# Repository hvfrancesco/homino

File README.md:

Homino
======

What is Homino?
---------------

Homino is a diy Arduino Duemilanove/Uno compatible board with some moloko vellocet addition
(e.g. featuring on-board 433Mhz RF transceiver for experiments on home-automation and microcontroller communication).
Homino is an open-hardware project by HVA (http://www.hv-a.com)

The board is based on Arduino open-hardware design, but revised in order to be made using a single-sided copper board and low-tech techniques like toner-transfer etching.
The connectors in Homino are arduino shields compatible, but the board comes in Altoids tin can format, so you can have the mints while soldering all those little components.

How does Homino compare to Arduino?
-----------------------------------

Homino replicates almost all the features of Atmega328 based Arduino, with a few design limitations:

- No on-board usb-to-ttl, you will need an external usb-ttl cable to program it or a serial port adapter that can handle RS232 level switching (however auto-reset works flawlessly)
- No ISP connector

There is fortunately some nice additions too:

- Selectable 5V/3.3V operation mode (through an old style jumper, we feared a slide switch could be more dangerous)
- On-board RF communication based on low-cost 433Mhz radio modules like the ones from SeeedStudio, allowing the interoperability with current low-cost 433 MHz remote controlled devices. Homino will most likely work with all 433Mhz popular power outlet sockets.
Communication between several Homino boards or any other 433Mhz RF enabled microcontroller is also very easily done through VirtualWire library.

How do I build Homino?
----------------------

Homino is designed to be built on a homemade custom produced pcb using single sided boards.
We successfully built several boards using tone-transfer method using a photocopier and common light magazine coated paper, you can use transparency film, but the magazine solution proved to be the most reliable and cheapest in our experience.
Homino board is rather dense and has some thin routes and small gaps between them, so it is not the easiest design to use with tone-transfer based etching, but if you're careful it works very well.

List of components:

- PCB single sided board (you can cut 3 Homino boards from a 160x100 sheet)
- 1 x Atmega328 MCU (use Atmega328P-PU for lower power consumption, Atmega328-PU will work fine anyway)
- 1 x 28 way DIL socket (optional but useful if you plan to remove or change the Atmega chip)
- 3 x 47uF capacitors
- 5 x 0,1 uF ceramic capacitors
- 2 x 22 pF ceramic capacitors
- 1 x 5V voltage regulator (7805 in TO-220 case)
- 1 x 3.3 V voltage regulator (LP2950 in TO-92 case)
- 1 x N4001 diode
- 2 x 1k resistor
- 1 x 10k resistor
- 2 x leds (using a blue led for power and a red one linked to digital pin13)
- 1 x 16Mhz crystal (a cheaper 16
Mhz ceramic resonator can be used, you could choose a 3-pin resonator and in that case you can probably omit the 22pF capacitors, but we like the crystal better)
- 1 power jack (optional)
- female pin sockets
- 1 x 6 way male pin header
- 1 x 3 way male pin header with jumper
- 1 x button for reset
- RF transmitter and receiver modules

The cost of the components is about 9,5 euros when bought in very small quantities from online distributors like Farnell or RS, if you buy larger quantities or have cheaper providers, the total cost can be quite lower. RF modules from SeeedStudio cost $4,9.
Ideal cost including RF modules should be around 12 US$.
You can buy Atmega328 chip already programmed with Arduino bootloader from several distributors or Arduino online store, but if you already own an Arduino or some kind of AVR programmer you can buy bare 328 chip and save a few euros. Burning the bootloader to an Atmega using another Arduino as ISP programmer, even if you are new to Arduino world, is a piece of cake if you follow this tutorial:
http://arduino.cc/en/Tutorial/ArduinoToBreadboard

The following image is a label you can simply print on self-adhesive paper and stick on top of your Homino board before soldering the components.

Useful links
------------

Arduino libraries for RF projects
- http://code.google.com/p/rc-switch/
- http://www.airspayce.com/mikem/arduino/

Low-cost RF modules compatible with Homino
- http://www.seeedstudio.com/depot/433mhz-rf-link-kit-p-127.html?cPath=19_22

Credits
-------

Homino is obviously Open Hardware, and all the files are distributed under a
<a rel="license" href="http://creativecommons.org/licenses/by-nc-sa/3.0/">Creative Commons Attribution-NonCommercial-ShareAlike 3.0 Unported License</a>
.

HVA lego-logo is property of 'HVA - hermanitos verdes architetti' (http://www.hv-a.com) and shouldn't be used without permission.

Homino is inspired and based on other Arduino compatible projects, for example:

http://hacks.ayars.org/2013/05/ayrduino-single-sided-arduino-clone.html
http://vonkonow.com/wordpress/2012/10/nanino-the-diy-friendly-arduino

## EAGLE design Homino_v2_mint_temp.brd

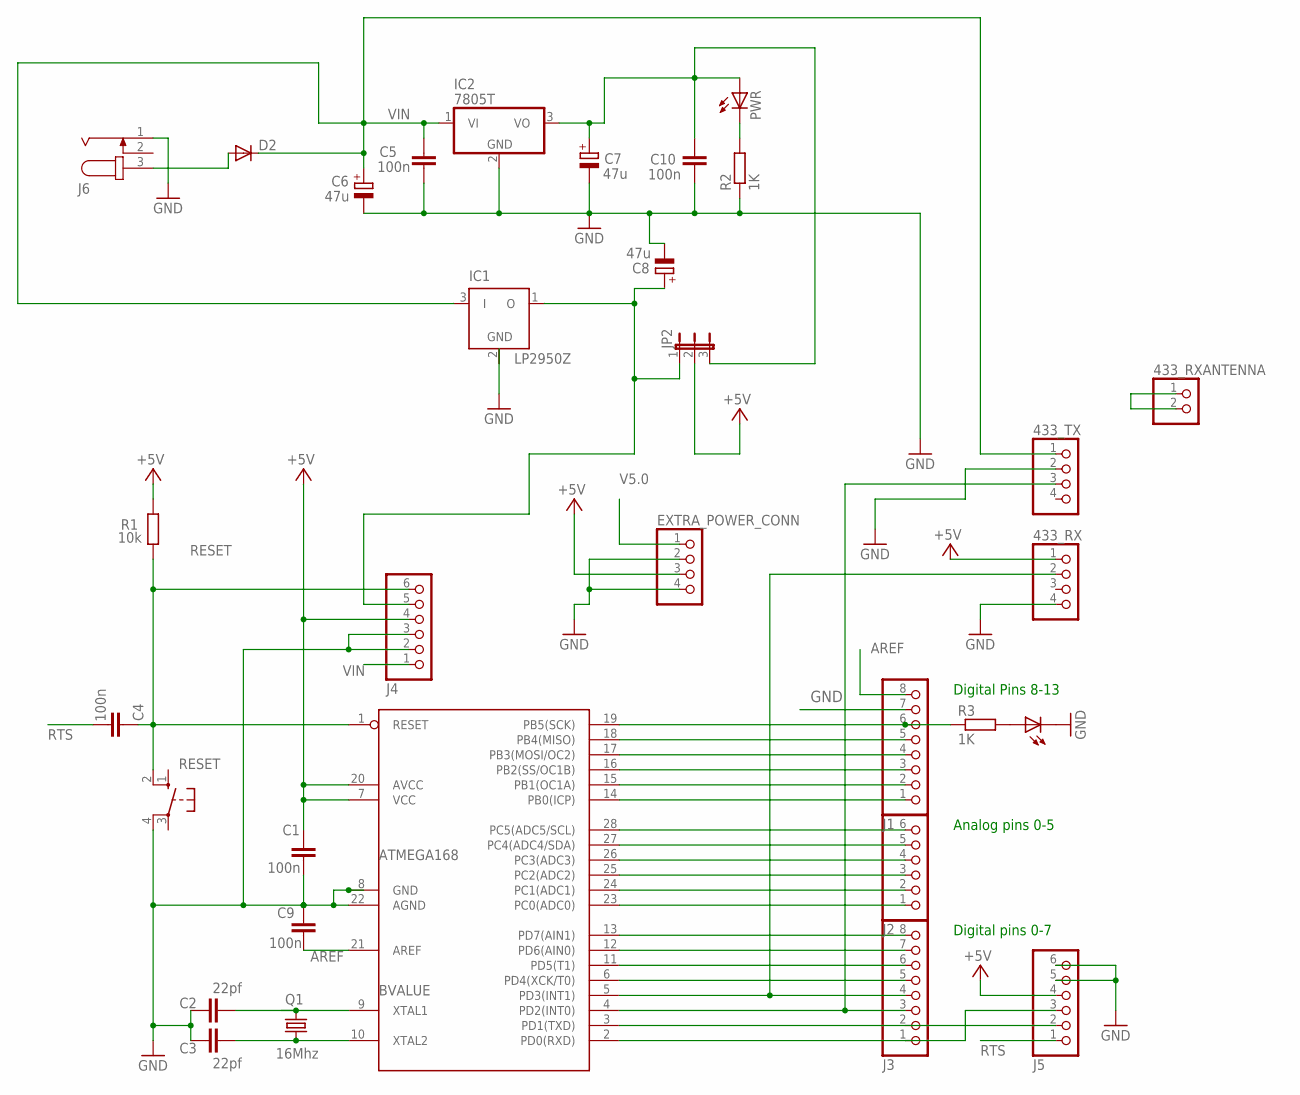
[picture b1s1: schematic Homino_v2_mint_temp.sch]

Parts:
433_RX, 433_TX: PINHD-1X4; 1X04
433_RXANTENNA: PINHD-1X2; 1X02
BVALUE: ATMEGA168; DIL28-3
C1, C4, C5, C9, C10: 100n; C050-024X044
C2, C3: 22pf; C025-024X044
C6, C7, C8: 47u; E3,5-8
D2: DIODE-C1702-05; C1702-05
EXTRA_POWER_CONN: PINHD-1X4; 1X04
IC1: LP2950Z; TO92
IC2: 7805T; TO220H
J1, J3: PINHD-1X8; 1X08
J2, J4, J5: PINHD-1X6; 1X06
J6: JACK-PLUG0; SPC4077
JP2: JP2E; JP2
P13: LED3MM
PWR: LED3MM
Q1: 16Mhz; HC49U-V
R1: 10k; 0204/7
R2, R3: 1K; 0204/5
RESET: 10-XX; B3F-10XX

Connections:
AREF: BVALUE.21 (AREF), C9.1, J1.8
DCV: 433_RX.1, BVALUE.7 (VCC), BVALUE.20 (AVCC), C1.1, EXTRA_POWER_CONN.3, J4.4, J5.4, JP2.2, R1.2
GND: 433_RX.4, 433_TX.2, BVALUE.8 (GND), BVALUE.22 (AGND), C1.2, C2.1, C3.1, C5.1, C6.-, C7.-, C8.-, C9.2, C10.1, EXTRA_POWER_CONN.2, EXTRA_POWER_CONN.4, IC1.2 (GND), IC2.2 (GND), J1.7, J4.2, J4.3, J5.5, J5.6, J6.1, P13.K (C), R2.1, RESET.4 (P1)
unnamed: BVALUE.2 (PD0(RXD)), J3.1, J5.3
unnamed: BVALUE.15 (PB1(OC1A)), J1.2
unnamed: PWR.K (C), R2.2
unnamed: D2.A, J6.3
unnamed: BVALUE.9 (XTAL1), C2.2, Q1.2
unnamed: P13.A, R3.2
unnamed: 433_TX.3, BVALUE.4 (PD2(INT0)), J3.3
unnamed: 433_RX.2, BVALUE.5 (PD3(INT1)), J3.4
unnamed: BVALUE.6 (PD4(XCK/T0)), J3.5
unnamed: BVALUE.11 (PD5(T1)), J3.6
unnamed: BVALUE.12 (PD6(AIN0)), J3.7
unnamed: BVALUE.13 (PD7(AIN1)), J3.8
unnamed: BVALUE.23 (PC0(ADC0)), J2.1
unnamed: BVALUE.24 (PC1(ADC1)), J2.2
unnamed: BVALUE.25 (PC2(ADC2)), J2.3
unnamed: BVALUE.26 (PC3(ADC3)), J2.4
unnamed: BVALUE.27 (PC4(ADC4/SDA)), J2.5
unnamed: BVALUE.28 (PC5(ADC5/SCL)), J2.6
unnamed: BVALUE.3 (PD1(TXD)), J3.2, J5.2
unnamed: BVALUE.16 (PB2(SS/OC1B)), J1.3
unnamed: 433_RXANTENNA.1, 433_RXANTENNA.2
unnamed: BVALUE.18 (PB4(MISO)), J1.5
unnamed: BVALUE.14 (PB0(ICP)), J1.1
unnamed: BVALUE.10 (XTAL2), C3.2, Q1.1
unnamed: BVALUE.17 (PB3(MOSI/OC2)), J1.4
RESET: BVALUE.1 (RESET), C4.1, J4.6, R1.1, RESET.2 (S1)
RTS: C4.2, J5.1
SCK: BVALUE.19 (PB5(SCK)), J1.6, R3.1
V3.3: C8.+, IC1.1 (O), J4.5, JP2.1
V5.0: C7.+, C10.2, EXTRA_POWER_CONN.1, IC2.3 (VO), JP2.3, PWR.A
VIN: 433_TX.1, C5.2, C6.+, D2.C, IC1.3 (I), IC2.1 (VI), J4.1

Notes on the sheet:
Analog pins 0-5
Digital Pins 8-13
Digital pins 0-7

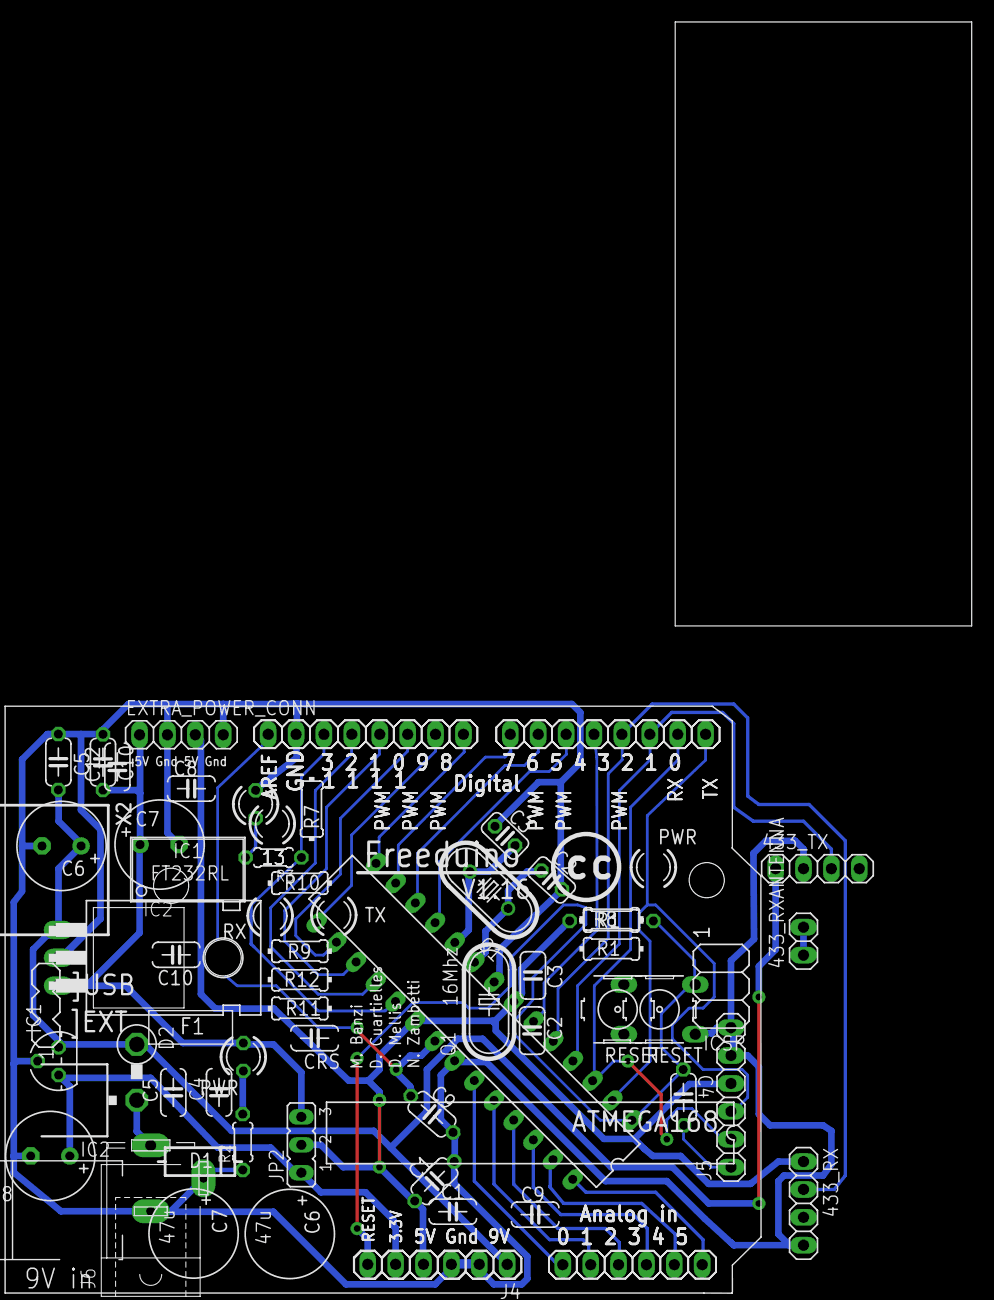
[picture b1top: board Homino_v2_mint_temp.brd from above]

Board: 2 copper layers, 32 parts (0 on the bottom side), 34 nets.

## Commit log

2013-06-23 added information to README
2013-06-23 adding markdown formatting to README
2013-06-23 testing different layout
2013-06-23 got rid of a jumper on V5.0 line, but maybe there is now a clearance problem with Vin through the voltage selection pin header
2013-06-24 rev.2 of board in beta status
2013-06-29 added note about logo
2013-06-29 fixed typo
2013-06-29 cleaned tree
2013-06-29 added single board images for tone tranfer and label print
2013-06-29 started adding information about board making
2013-06-29 added list of components
2013-06-29 minor changes
2013-06-29 fixed README
2013-06-29 more README info
2013-06-29 added some notes to components list

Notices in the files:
README.md:
CC BY-NC-SA 3.0
